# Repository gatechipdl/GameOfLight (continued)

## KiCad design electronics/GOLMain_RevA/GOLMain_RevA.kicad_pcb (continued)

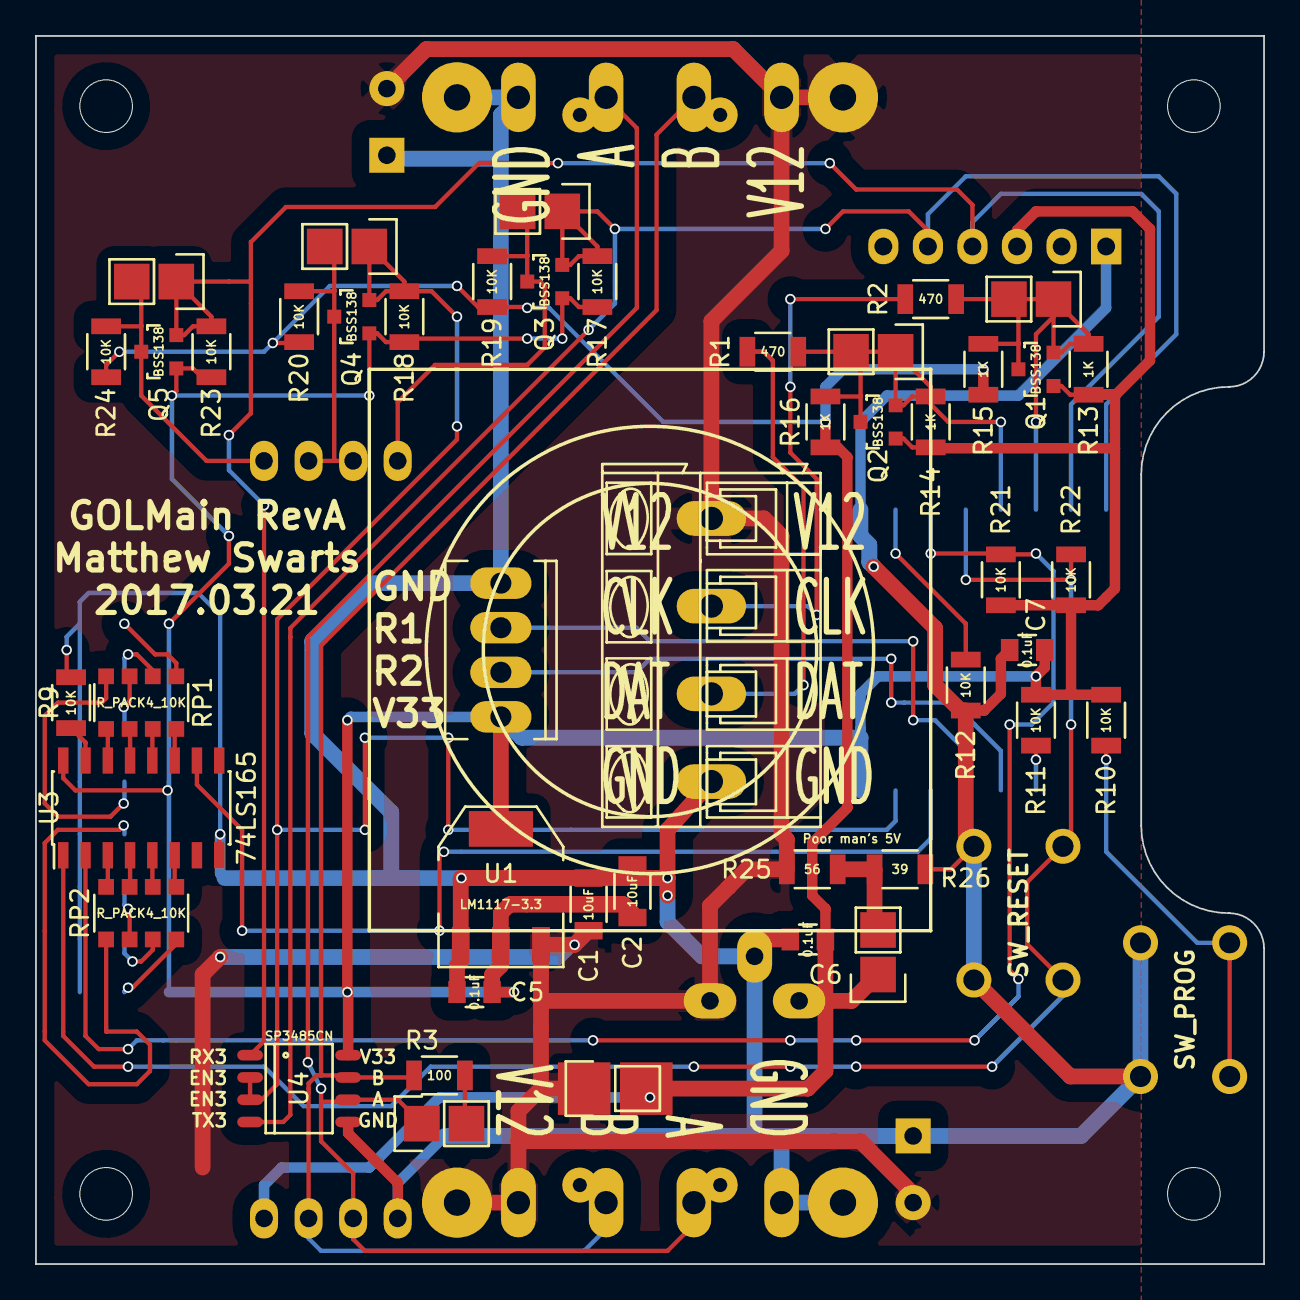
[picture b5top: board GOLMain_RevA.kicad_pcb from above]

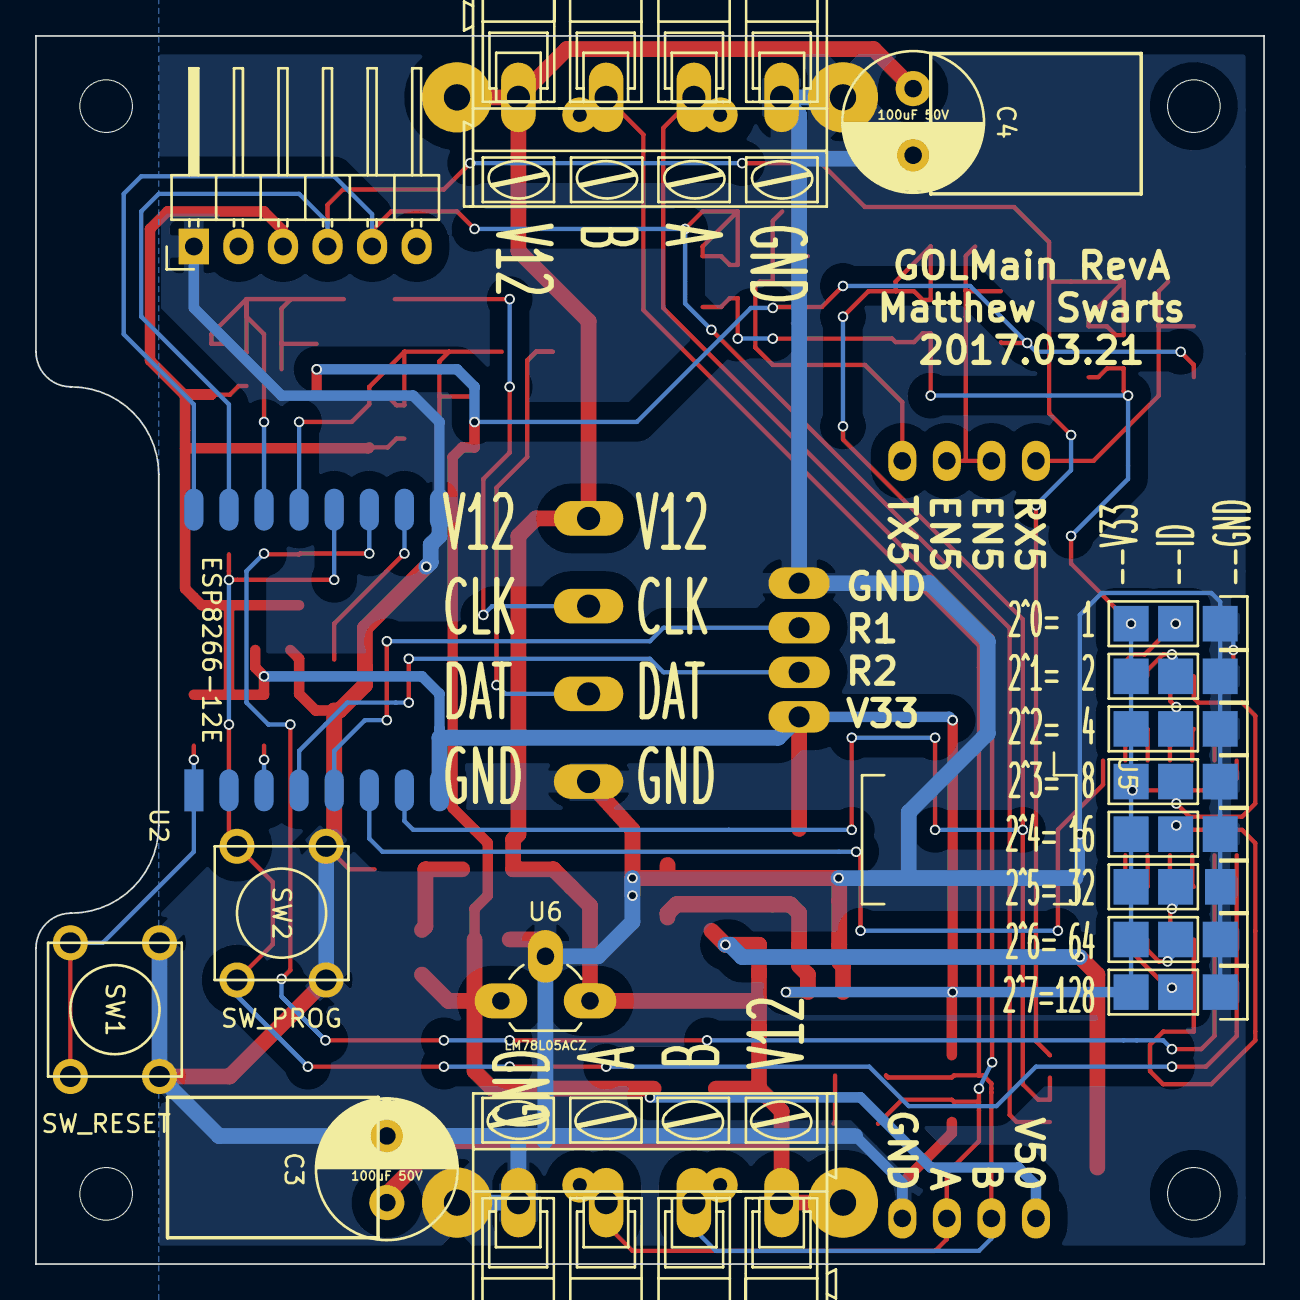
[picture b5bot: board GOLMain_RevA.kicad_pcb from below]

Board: 2 copper layers, 70.0 x 70.0 mm, 72 parts (18 on the bottom side), 43 nets.

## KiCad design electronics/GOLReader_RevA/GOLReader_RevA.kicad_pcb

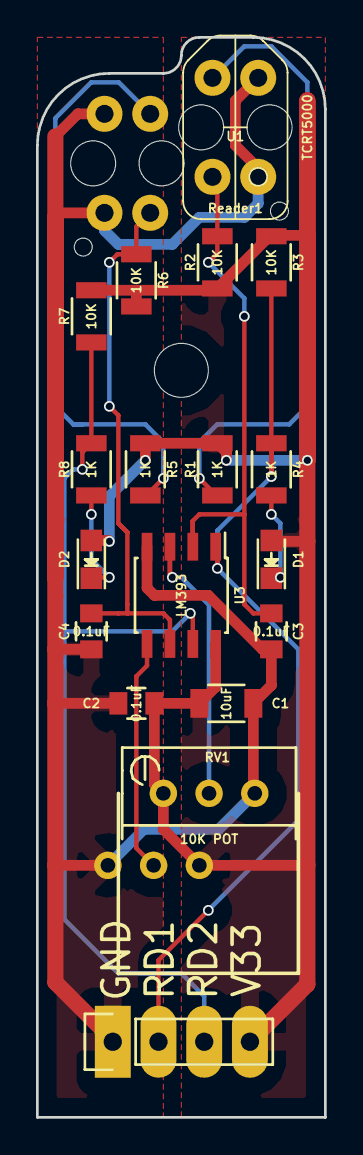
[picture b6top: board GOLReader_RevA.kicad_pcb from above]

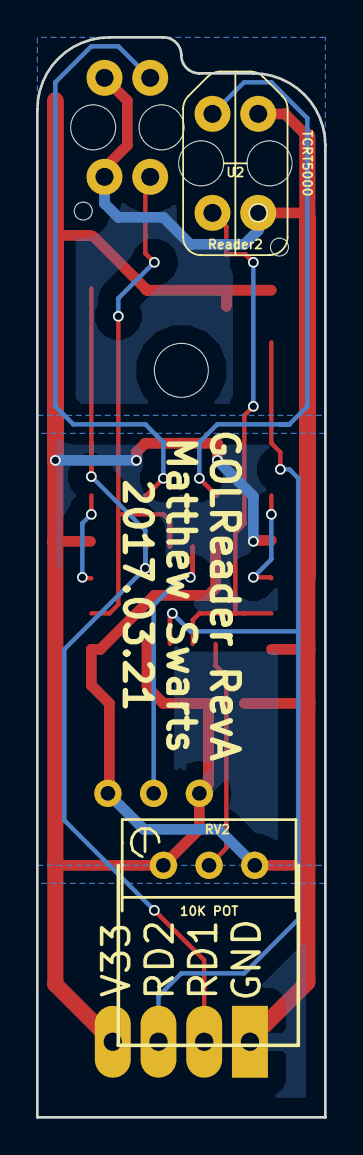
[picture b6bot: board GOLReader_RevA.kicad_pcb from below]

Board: 2 copper layers, 16.0 x 60.0 mm, 20 parts (2 on the bottom side), 12 nets.

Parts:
C1: 10uF; C_1206
C2, C3, C4: 0.1uF; C_0805
D1, D2: LED; LED-0805
P1: CONN_01X04; Pin_Header_Straight_1x04
R1, R4, R5, R8: 1K; R_1206
R2, R3, R6, R7: 10K; R_1206
RV1, RV2: 10K POT; Potentiometer_Bourns_3296W_3-8Zoll_Inline_ScrewUp
U1, U2: TCRT5000
U3: LM393; SOIC-8_3.9x4.9mm_Pitch1.27mm

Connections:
GND: C1.2, C2.2, C3.2, C4.2, P1.1, RV1.3, RV2.3, U1.2, U1.3, U2.2, U2.3, U3.4
unnamed: C3.1, R2.2, U1.4, U3.2
unnamed: C4.1, R6.2, U2.4, U3.6
unnamed: D1.1, R4.1
unnamed: D2.1, R8.1
unnamed: R1.2, U1.1
unnamed: R5.2, U2.1
unnamed: RV1.2, U3.3
unnamed: RV2.2, U3.5
READER1: P1.2, R3.2, R4.2, U3.1
READER2: P1.3, R7.2, R8.2, U3.7
V33: C1.1, C2.1, D1.2, D2.2, P1.4, R1.1, R2.1, R3.1, R5.1, R6.1, R7.1, RV1.1, RV2.1, U3.8

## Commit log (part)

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2017-02-09 initial renders, lantern fabrication, processing sketch
2017-02-25 added draft sketch of esp8266 based solution
2017-02-25 added initial bill of materials mostly consisting of the electronics and power systems with estimated parts list
2017-02-25 updated schematic and layout for proposed RevA
2017-03-10 updated main board schematic and layout
2017-03-11 updated schematics and part selection for layout
2017-03-18 updated main pcb to final version
2017-03-22 refined main board, shift 4 pin led conn, made more space for gnd and v12 planes; created tcrt5000 module
2017-03-22 added panelization of 12 units of the GOLReader, to cut pcb fabrication cost in half
2017-03-27 Create test
2017-03-27 Version 1 Lamp Files
2017-03-27 Lamp Version 3 Files
2017-04-04 added basic station string test firmware
2017-04-16 added GOLStationSerialEventTest to test serial events through FTDI or RS485 connection. Should send a byte through serial connection and will do a color wipe with that hue value on the color wheel
2017-04-16 forgot to add the serialEvent function to capture serial events for the GOLStationSerialEventTest
2017-04-18 added dual reader test sketch
2017-04-18 corrected led count to 45 in text sketches; added rs485 LOW on pin 13 for listening for stations; added pcb design for a power link to power the rs485 rails for a usb connector
2017-04-26 fixed a few indexing values in FiveSegmentRGB firmware; created test java processing sketch to send out test colors over serial
2017-04-26 processing and arduino sketches working for id responsive 5 segment strips with 540 byte packets; needs serial double buffer optimization to avoid serial buffer overflow in esp8266 of 128bytes
2017-04-26 make the setPixelColor method spread out over multiple loops
2017-04-27 working firmware for stations to accept 540 byte array through rs485 serial line at 57600 baud rate; and includes working processing java sketch to transmit that 540 byte array as an example
2017-04-29 Old python code that uses the Twitter Streaming API to trigger light patterns
2017-05-01 Added processing base sketch for communicating to stations
    Also added two games, conway and city.
2017-05-01 modified power board to fit mill better
2017-05-01 fixed bugs and included station change animation
2017-05-02 added update psu pcb and svg file
2017-05-02 firmware update, increased baud to 115200, disabled wifi, added more checks and recovery on errors in serial data received
2017-05-03 integrated fastled crgb fill_solid code. should work I think
2017-05-03 working FastLED implementation with 50ms delay ok, still all zero array byte not successful
2017-05-03 added modbus slave and master tests; not working yet
2017-05-03 integrated a diff and dediff differencing encoding scheme to deal with zeros in the uart byte array
2017-05-03 successfully integrated the diff64 into the firmware and an example processing sketch
2017-05-03 attempted to build terminator
2017-05-16 Processing sketches used at CHI 2017
2017-05-31 added node implementation with socket.io with server and firmware
2017-06-14 added more server side socket.io methods for emitting colors to the stations
2017-06-27 implemented byte based implementation of socketio client comms of five segment color transmission per station id; compiles, not tested; node server contains all emit functions;
2017-06-28 fixed doStuff interval test function on webserver for testing
2017-06-28 added LOTreeSocket code with working socket.io events using base64 decoding
2017-07-06 made some updates to a rainbow demo
2017-07-06 beginning of OTA setup
2017-07-06 new base.bin
2017-07-07 preprared webserver to host new binaries of firmware
2017-07-07 minor webserver updates
2017-07-07 minor updates to eeprom clearning and station id and hardware reset functions
2017-07-11 added udp base firmware along with custom base64 single character map demap
2017-07-24 added serverside test code for looking at light colors from two weeks ago
2017-07-31 some stuff leftover
2017-08-09 udp code sending to clients through socket.io address info
2017-08-10 new LO shade fabrication files
2017-08-10 test with feather 32u4 linking cap to LED
2017-08-10 updated test with animation
2017-08-14 mpr121 test on feather
2017-08-15 added mpr121 esp8266 working firmware code sample
2017-08-15 fixed conditional bug
2017-08-15 fixed bug (again) (sorry)
2017-08-15 added strandtest startup to base firmware
2017-08-15 changed wifimulti to just wifi and added binary export for server
2017-08-18 pushed IDSA demo station code
2017-08-18 latest firmware version 1006
2017-08-18 updated server with sample test.html for socket.io controls
2017-08-18 updated server
2017-09-01 integrated capsense control mode into LOTreeBase firmware and updated webserver to version 1007
2017-09-01 version 1008, added 20 retry skip on mpr121 setup while loop
2017-09-02 version 1009, removed udp processing; converted hsv floats to 255 bytes for FastLED's CHSV method
2017-09-02 version 1011; cleaned up variables and naming; added function prototypes; swapped library order of FastLED and Wire; added FASTLED_INTERRUPT_RETRY_COUNT 1 before FastLED.h library include
2017-09-02 version 1012; removed wire and mpr121 libraries and references;
2017-09-02 version 1013; added wire library and begin calls back in, since rainbow strandtest was working with version 1012
2017-09-02 version 1013; this commit includes the compiled bin file
2017-09-02 version 1014; added MPR121 library back in, and added the MPR121 setup calls
2017-09-02 version 1016; added FASTLED_ALLOW_INTERRUPTS 0 before FastLED include; changed server to push currently specified version, regardless of greater than sequence
2017-09-02 fastLED and MPR121 test
2017-09-02 correct hsv values to be between 0-255
2017-09-02 corrected LED index to sets of 9 in 5 layers
2017-09-03 version 1017; modified LO_mpr121_and_fastLED_test_cz to match variable format for simpler compatability - needs verification that it still works; modified webserver to use the base0000.bin file based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
2017-09-04 version 1019; changed first operation mode to CapSenseControl instead of StrandTest1
2017-09-04 added basic wifi connection to orchard to the LO_mpr121_and_fastLED_test_cz.ino
2017-09-04 version 1020; cut out udp and a few socketio methods; removed 2 minute updatecheck; removed redraw and made all direct calls to FastLed.show(); added eeprom to LO_mpr121_and_fastLED_test_cz.ino
2017-09-04 version 2001 and 3001; 2001 has websockets removed and libaries minimized to match mpr121 test code; 3001 has OTA added to the mpr121 test code, but does not contain function delegates; otherwise pre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
2017-09-06 version 3005; successfully merged code bases for socket io and operation function delegation along with the cap sense painting code
2017-09-06 added client side fps framerate socket.io transmission testing in test.html
2017-09-12 minor update
2017-09-12 added comma
2017-09-12 more minor changes
2017-09-12 version 3006; added capSense emit methods and tracking for capSense states; modified how stations subscribe so that we have better chance of retrieving station info
2017-09-12 added request station info button to manager.html; added five color input sample to test.html
2017-09-12 merged station data if exists, else add data to stationData json; integrated save station data into manager.html
2017-09-12 version 3008; reduced check updates to only explicit; corrected column headers in manager.html; added online to false on station disconnect; began to look into socket id emit method
2017-09-12 version 3009; added capsensetest without emit functions and resorted the operation modes in both firmware, server, and web pages; changed io.to(socketid) to socket.broadcast.to(socketid)
2017-09-12 updated manager.html with onlick instead of onchange for ping and update buttons; added console logging to managerial socketio method events from web browsers
2017-09-13 modified stationid command on server side to convert uint16array to uint8array for compression to base64
2017-09-13 version 3010; swapped bit shifting order of setStationId inputs
2017-09-13 version 3012; stationId = (binPayload[0]<<8) | (binPayload[1]<<0);
2017-09-13 version 3013; ((binPayload[0]<<0) & 0xFF) + ((binPayload[1]<<8 & 0xFF00)
2017-09-13 resolved setStationMode issue on manager by adding command setMode to emit; resolved fiveColor issue on test.html to changing to socket.broadcast.to(socket).emit(...
2017-09-13 replaced socketid with the correct stationid in the setGiveColorsListener method
2017-09-13 version 3014; added chunkedDelays to eeprom reading and writing of integers; added 'color ripple' button to test.html that ripples the selected color from 0 to 24 at 200ms
2017-09-14 version 3015; added firmware method for capsensetop only; modified capsensecontrol operation to only do emits, no lighting; created rainbow surge button on test.html; added socketio method on server 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
2017-10-17 version 3016 ready for gvu demo
2017-12-07 testCapSense.html and other client side updates
2017-12-09 Cap Sense at Boulder
2017-12-09 boulder push 2
2017-12-09 removed two intervals
2017-12-09 set brightness
2017-12-09 consolidate capsense
2017-12-09 set color change interval
2017-12-09 restart boulder
2017-12-09 button
2017-12-09 even quicker
2017-12-11 added test3.html with captest toggle functioning; added beginning of an orchard.js client-side api
2018-03-01 renamed functions to match Requirements doc for SetFiveColors, CapSenseEvent, CapSenseTouch, and CapSenseUnTouch and implemented CapSenseTouch and CapSenseUnTouch
2018-03-05 added some api descriptions
2018-03-06 added more detail to server documentation for api development
2018-03-08 added examples code to server readme
2018-03-08 small correction on single quote
2018-03-12 added logger.html to log relevant socket.io events; modified server to broadcast out SetFiveColors events; modified some test html files to match the current 'API'
2018-03-24 pushed client side emulator
2018-03-25 added game of light and trigger types
2018-03-26 added socket function
2018-03-26 merging emulator into server folder
2018-03-26 changed animation interval and socket call
2018-03-26 console logging in browser
2018-03-26 udpate
2018-03-26 update all stations for button clicks
2018-03-26 less efficient GOL
2018-03-26 comparison version GOL
2018-03-26 cap events added to emu
2018-03-28 updated logging and GoL
2018-03-30 added export log and bookmark capability
2018-03-30 fixed menu error with paint/ranibow scripts
2018-03-31 updated rom loading
2018-03-31 moved rainbow.js to roms folder
2018-03-31 new rainbow.js with top cap animation
2018-03-31 fixed bug
2018-04-02 experimental rainbow 2 rom
    sends updates to only one station per animation loop. Will this ease the
    socket burden?
2018-04-02 edit
2018-04-03 added UDP routing over port 30000 for SetFivesUDP() method on the server; added UDP receiving and parsing of data packet on firmware with command byte 5
2018-04-03 Matt's UPD update, afects emulator and toggle five
2018-04-03 Added heatmap.js to simulate a heatmap - just based on random numbers
2018-09-26 added audiosynth.js and a rainbowSynth ROM to make basic music on the top cap sensors
2019-02-16 4x6 updates
    changed script files in emulator to support 4x6 config, hard-coded
    station order into stations.json
2019-03-01 beginning of next gen electronics base for power, but not much
2019-03-07 Update to firmware base4000 to support new 192.168.1.1 gateway
2019-03-07 a little refactoring to consistent camelCase
2019-03-07 base4001, moved eeprom read of station id to first thing in setup on firmware; it was at the end of setup for some reason
2019-03-08 replaced station_id with stationId; updated check on ip address stored in _stationData to make sure it is a string and not a number - newer esp8266 ip method returns a better formatted string rather 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
2019-03-08 refactored station_id to stationId onto socket-script.js too
2019-03-08 base4009, many updates to smooth setup with mpr121 and fastled interrupts
2019-03-09 added water rom
